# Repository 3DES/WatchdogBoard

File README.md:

Watchdog PCB, has 8 outputs and 4 inputs. The first output is used as watchdog output and will be switched off if not triggered regularely. Input 0 is the watchdog readback to check if the watchdog can still switch off the output 0 relay.

The relays are powered via USB 5V, what, depending on the used USB cable, can be a bit less sometimes. If you have problems with that change the USB cable or change the layout:

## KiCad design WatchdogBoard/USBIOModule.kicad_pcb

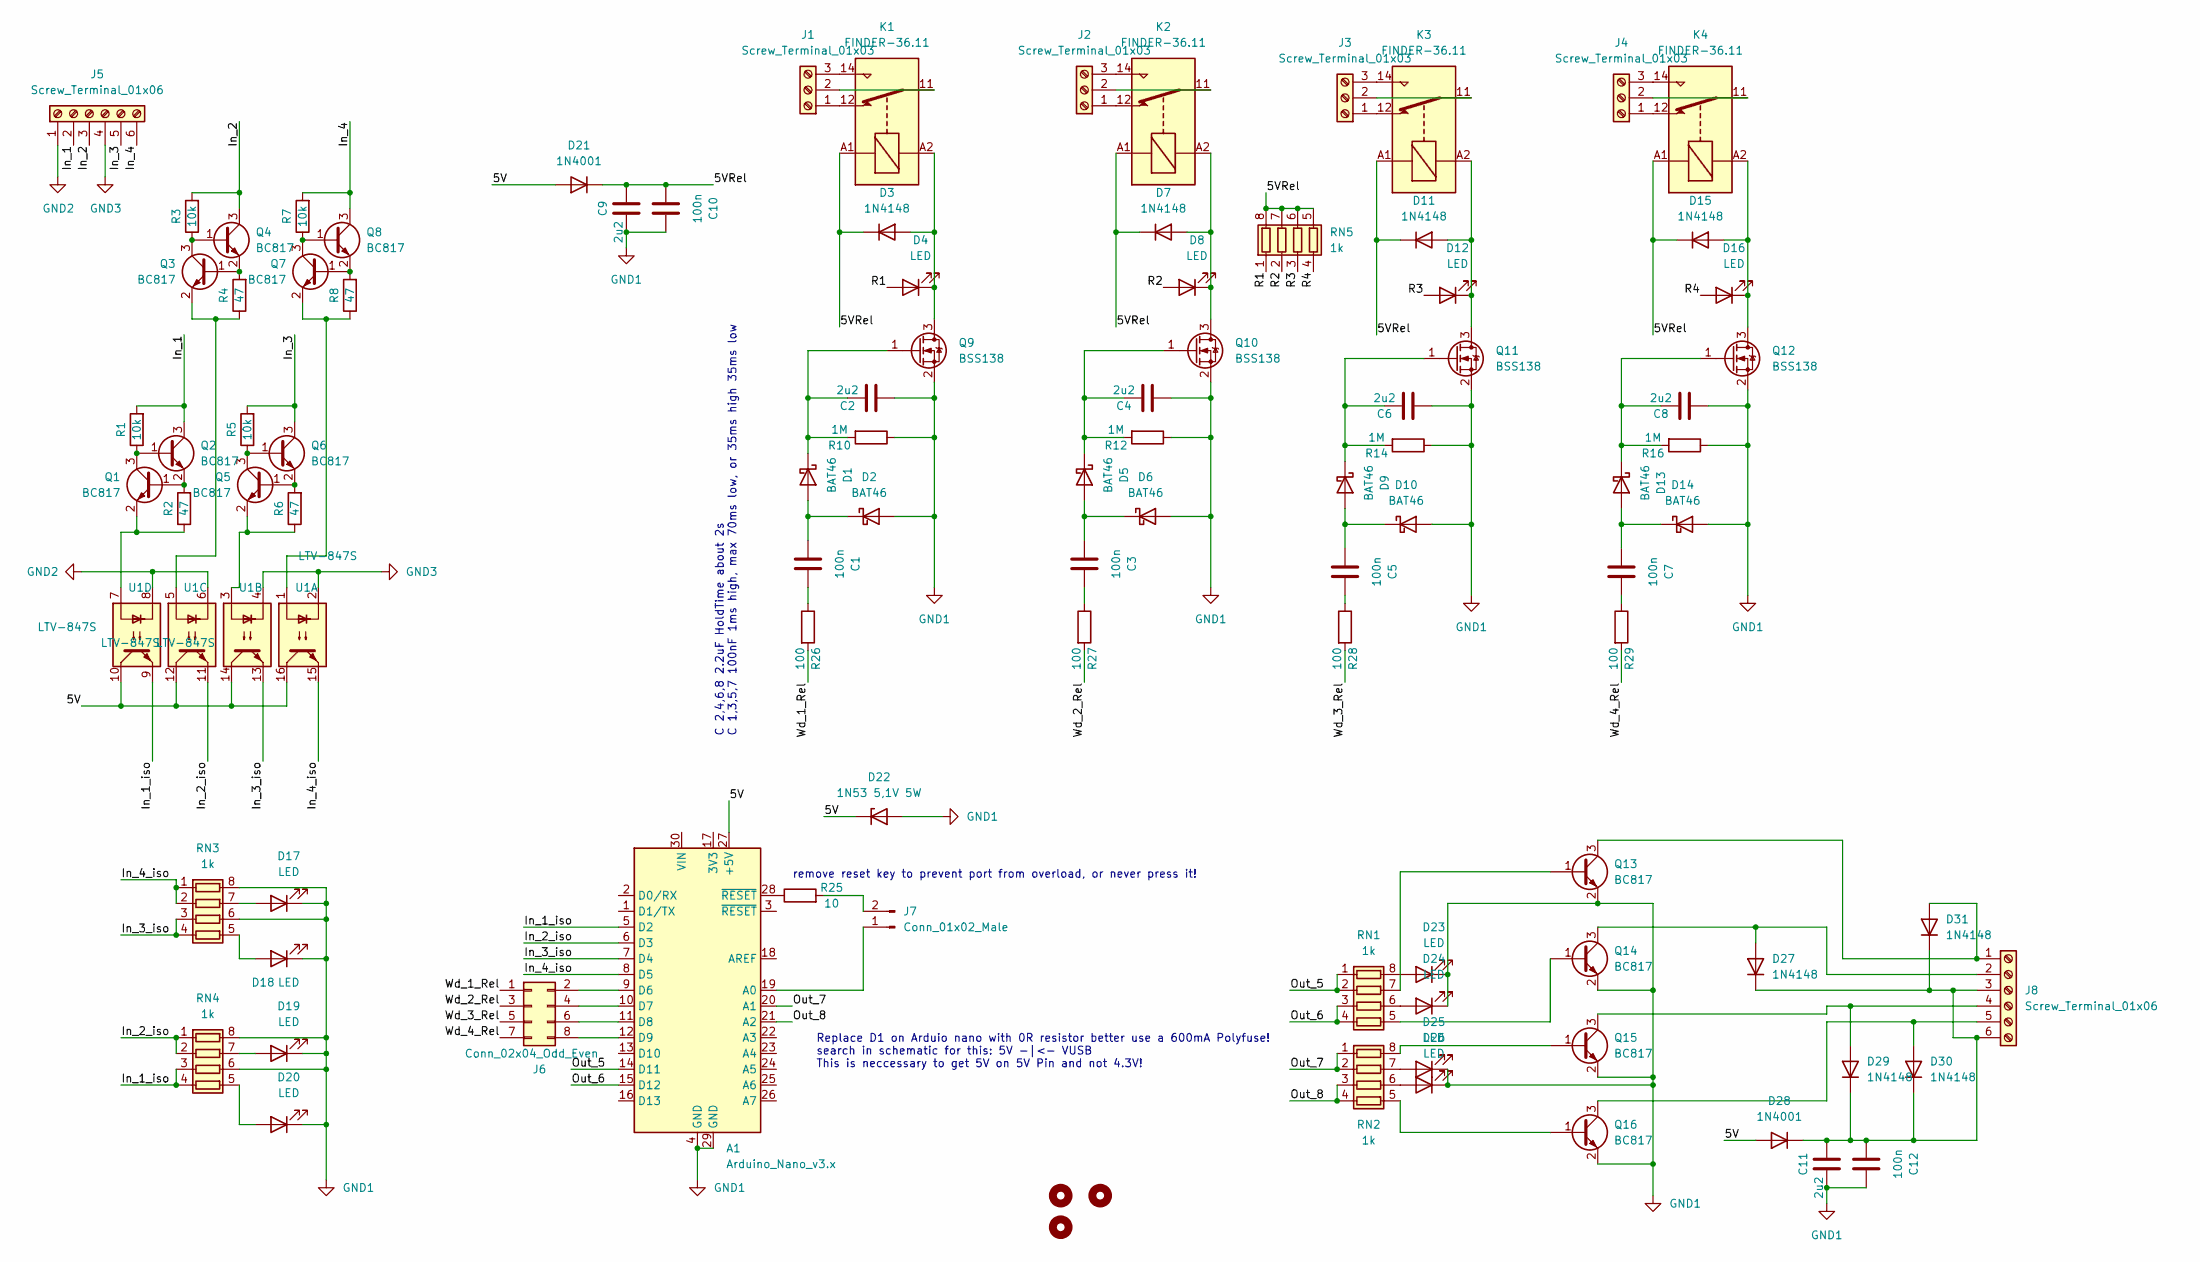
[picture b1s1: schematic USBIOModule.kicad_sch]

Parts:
A1: Arduino_Nano_v3.x; Arduino_Nano
C1, C3, C5, C7, C10, C12: 100n; C_0603_1608Metric
C2, C4, C6, C8, C9, C11: 2u2; C_0603_1608Metric
D1, D2, D5, D6, D9, D10, D13, D14: BAT46; D_SOD-123
D3, D7, D11, D15, D27, D29, D30, D31: 1N4148; D_MiniMELF
D4, D8, D12, D16, D17, D18, D19, D20, D23, D24, D25, D26: LED; LED_0603_1608Metric
D21, D28: 1N4001; D_DO-41_SOD81_P10.16mm_Horizontal
D22: 1N53 5,1V 5W; D_DO-41_SOD81_P10.16mm_Horizontal
H1, H2, H3: MountingHole; MountingHole_3.2mm_M3
J1, J2, J3, J4: Screw_Terminal_01x03; TerminalBlock_bornier-3_P5.08mm
J5, J8: Screw_Terminal_01x06; TerminalBlock_bornier-6_P5.08mm
J6: Conn_02x04_Odd_Even; PinHeader_2x04_P2.54mm_Vertical
J7: Conn_01x02_Male; PinHeader_1x02_P2.54mm_Vertical
K1, K2, K3, K4: FINDER-36.11; Relay_SPDT_Finder_36.11
Q1, Q2, Q3, Q4, Q5, Q6, Q7, Q8, Q13, Q14, Q15, Q16: BC817; SOT-23
Q9, Q10, Q11, Q12: BSS138; SOT-23
R1, R3, R5, R7: 10k; R_0603_1608Metric
R2, R4, R6, R8: 47; R_0603_1608Metric
R10, R12, R14, R16: 1M; R_0603_1608Metric
R25: 10; R_0603_1608Metric
R26, R27, R28, R29: 100; R_0603_1608Metric
RN1, RN2, RN3, RN4, RN5: 1k; R_Array_Convex_4x0612
U1: LTV-847S; SMDIP-16_W9.53mm

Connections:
/5V: A1.27 (+5V), D21.2 (A), D22.1 (K), D28.2 (A), U1.10, U1.12, U1.14, U1.16
/5VRel: C9.2, C10.1, D3.1 (K), D7.1 (K), D11.1 (K), D15.1 (K), D21.1 (K), K1.A1, K2.A1, K3.A1, K4.A1, RN5.5 (R4.2), RN5.6 (R3.2), RN5.7 (R2.2), RN5.8 (R1.2)
/In_1: J5.2, Q2.3 (C), R1.2
/In_1_iso: A1.5 (D2), RN4.3 (R3.1), RN4.4 (R4.1), U1.9
/In_2: J5.3, Q4.3 (C), R3.2
/In_2_iso: A1.6 (D3), RN4.1 (R1.1), RN4.2 (R2.1), U1.11
/In_3: J5.5, Q6.3 (C), R5.2
/In_3_iso: A1.7 (D4), RN3.3 (R3.1), RN3.4 (R4.1), U1.13
/In_4: J5.6, Q8.3 (C), R7.2
/In_4_iso: A1.8 (D5), RN3.1 (R1.1), RN3.2 (R2.1), U1.15
/Out_5: A1.14 (D11), RN1.1 (R1.1), RN1.2 (R2.1)
/Out_6: A1.15 (D12), RN1.3 (R3.1), RN1.4 (R4.1)
/Out_7: A1.20 (A1), RN2.1 (R1.1), RN2.2 (R2.1)
/Out_8: A1.21 (A2), RN2.3 (R3.1), RN2.4 (R4.1)
/R1: D4.2 (A), RN5.1 (R1.1)
/R2: D8.2 (A), RN5.2 (R2.1)
/R3: D12.2 (A), RN5.3 (R3.1)
/R4: D16.2 (A), RN5.4 (R4.1)
/Wd_1_Rel: J6.1, R26.2
/Wd_2_Rel: J6.3, R27.2
/Wd_3_Rel: J6.5, R28.2
/Wd_4_Rel: J6.7, R29.2
GND1: A1.4 (GND), A1.29 (GND), C2.2, C4.2, C6.2, C8.2, C9.1, C10.2, C11.1, C12.2, D2.2 (A), D6.2 (A), D10.2 (A), D14.2 (A), D17.1 (K), D18.1 (K), D19.1 (K), D20.1 (K), D22.2 (A), D23.1 (K), D24.1 (K), D25.1 (K), D26.1 (K), Q9.2 (S), Q10.2 (S), Q11.2 (S), Q12.2 (S), Q13.2 (E), Q14.2 (E), Q15.2 (E), Q16.2 (E), R10.1, R12.1, R14.1, R16.1, RN3.6 (R3.2), RN3.8 (R1.2), RN4.6 (R3.2), RN4.8 (R1.2)
GND2: J5.1, U1.6, U1.8
GND3: J5.4, U1.2, U1.4
unnamed: A1.9 (D6), J6.2
unnamed: A1.10 (D7), J6.4
unnamed: A1.11 (D8), J6.6
unnamed: A1.12 (D9), J6.8
unnamed: A1.19 (A0), J7.1
unnamed: A1.28 (~RESET), R25.1
unnamed: C1.1, D1.2 (A), D2.1 (K)
unnamed: C1.2, R26.1
unnamed: C2.1, D1.1 (K), Q9.1 (G), R10.2
unnamed: C3.1, D5.2 (A), D6.1 (K)
unnamed: C3.2, R27.1
unnamed: C4.1, D5.1 (K), Q10.1 (G), R12.2
unnamed: C5.1, D9.2 (A), D10.1 (K)
unnamed: C5.2, R28.1
unnamed: C6.1, D9.1 (K), Q11.1 (G), R14.2
unnamed: C7.1, D13.2 (A), D14.1 (K)
unnamed: C7.2, R29.1
unnamed: C8.1, D13.1 (K), Q12.1 (G), R16.2
unnamed: C11.2, C12.1, D27.1 (K), D28.1 (K), D29.1 (K), D30.1 (K), D31.1 (K), J8.3, J8.6
unnamed: D3.2 (A), D4.1 (K), K1.A2, Q9.3 (D)
unnamed: D7.2 (A), D8.1 (K), K2.A2, Q10.3 (D)
unnamed: D11.2 (A), D12.1 (K), K3.A2, Q11.3 (D)
unnamed: D15.2 (A), D16.1 (K), K4.A2, Q12.3 (D)
unnamed: D17.2 (A), RN3.7 (R2.2)
unnamed: D18.2 (A), RN3.5 (R4.2)
unnamed: D19.2 (A), RN4.7 (R2.2)
unnamed: D20.2 (A), RN4.5 (R4.2)
unnamed: D23.2 (A), RN1.8 (R1.2)
unnamed: D24.2 (A), RN1.6 (R3.2)
unnamed: D25.2 (A), RN2.7 (R2.2)
unnamed: D26.2 (A), RN2.6 (R3.2)
unnamed: D27.2 (A), J8.2, Q14.3 (C)
unnamed: D29.2 (A), J8.4, Q15.3 (C)
unnamed: D30.2 (A), J8.5, Q16.3 (C)
unnamed: D31.2 (A), J8.1, Q13.3 (C)
unnamed: J1.1, K1.12
unnamed: J1.2, K1.11
unnamed: J1.3, K1.14
unnamed: J2.1, K2.12
unnamed: J2.2, K2.11
unnamed: J2.3, K2.14
unnamed: J3.1, K3.12
unnamed: J3.2, K3.11
unnamed: J3.3, K3.14
unnamed: J4.1, K4.12
unnamed: J4.2, K4.11
unnamed: J4.3, K4.14
unnamed: J7.2, R25.2
unnamed: Q1.1 (B), Q2.2 (E), R2.2
unnamed: Q1.2 (E), R2.1, U1.7
unnamed: Q1.3 (C), Q2.1 (B), R1.1
unnamed: Q3.1 (B), Q4.2 (E), R4.2
unnamed: Q3.2 (E), R4.1, U1.5
unnamed: Q3.3 (C), Q4.1 (B), R3.1
unnamed: Q5.1 (B), Q6.2 (E), R6.2
unnamed: Q5.2 (E), R6.1, U1.3
unnamed: Q5.3 (C), Q6.1 (B), R5.1
unnamed: Q7.1 (B), Q8.2 (E), R8.2
unnamed: Q7.2 (E), R8.1, U1.1
unnamed: Q7.3 (C), Q8.1 (B), R7.1
unnamed: Q13.1 (B), RN1.7 (R2.2)
unnamed: Q14.1 (B), RN1.5 (R4.2)
unnamed: Q15.1 (B), RN2.8 (R1.2)
unnamed: Q16.1 (B), RN2.5 (R4.2)

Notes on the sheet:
C 2,4,6,8 2.2uF HoldTime about 2s C 1,3,5,7 100nF 1ms high, max 70ms low, or 35ms high 35ms low
Replace D1 on Arduio nano with 0R resistor better use a 600mA Polyfuse! search in schematic for this: 5V -|<- VUSB This is neccessary to get 5V on 5V Pin and not 4.3V!
remove reset key to prevent port from overload, or never press it!

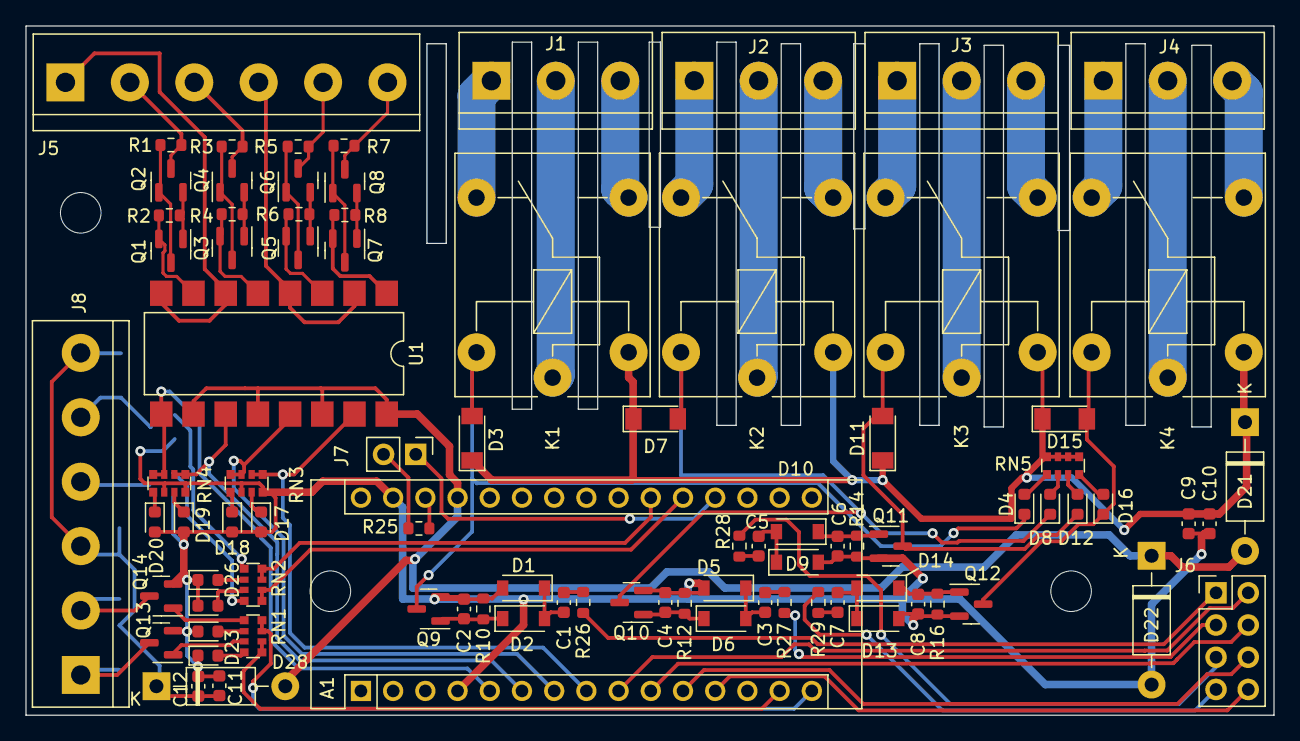
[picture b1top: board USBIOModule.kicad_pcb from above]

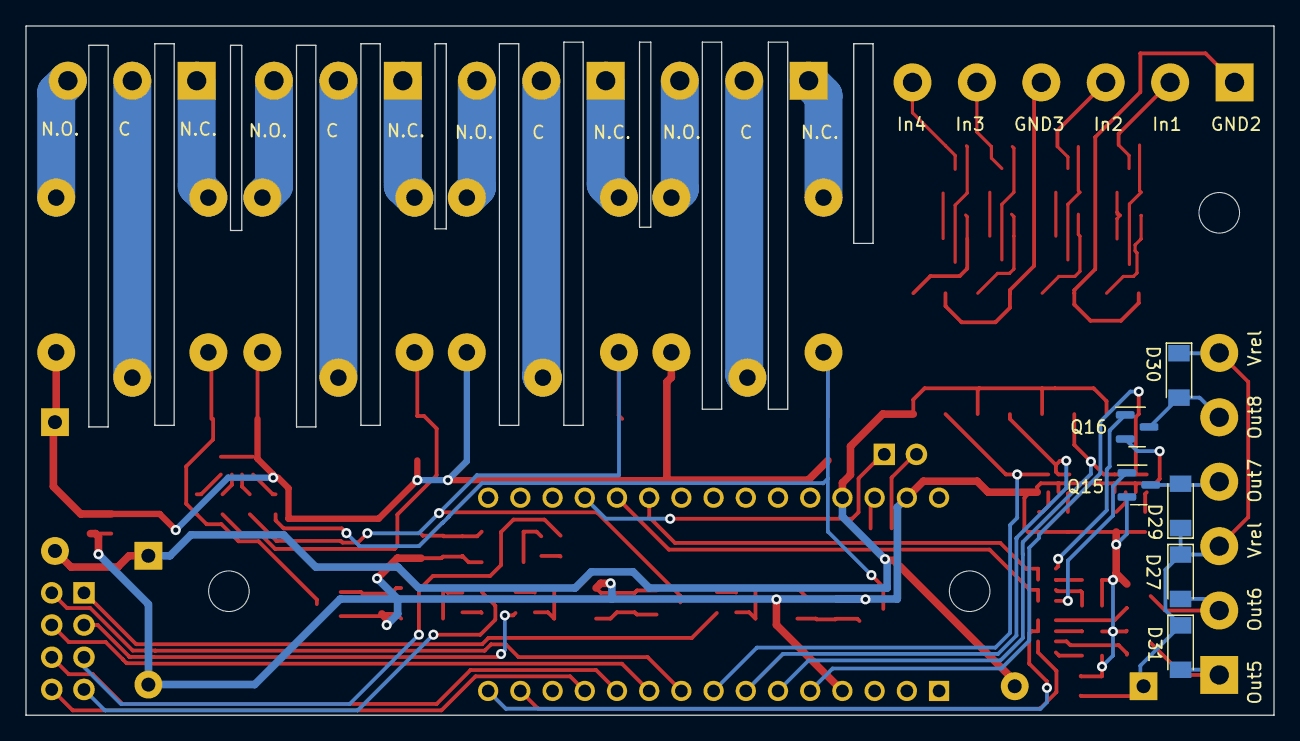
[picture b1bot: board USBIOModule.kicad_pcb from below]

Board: 2 copper layers, 98.4 x 54.4 mm, 98 parts (6 on the bottom side), 89 nets.

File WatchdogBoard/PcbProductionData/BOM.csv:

"ID";"Bezeichner";"Gehäuse";"Stückzahl";"Bezeichnung";"Anbieter und Referenz";
1;"J5,J8";"TerminalBlock_bornier-6_P5.08mm";2;"Screw_Terminal_01x06";;;
2;"RN1,RN5,RN2,RN4,RN3";"R_Array_Convex_4x0612";5;"1k";;;
3;"K4,K2,K1,K3";"Relay_SPDT_Finder_36.11";4;"FINDER-36.11";;;
4;"Q9,Q10,Q12,Q11";"SOT-23";4;"BSS138";;;
5;"D3,D11,D7,D15,D29,D30,D31,D27";"D_MiniMELF";8;"1N4148";;;
6;"R2,R6,R4,R8";"R_0603_1608Metric";4;"47";;;
7;"Q5,Q3,Q8,Q14,Q2,Q6,Q7,Q1,Q13,Q4,Q15,Q16";"SOT-23";12;"BC817";;;
8;"R1,R7,R3,R5";"R_0603_1608Metric";4;"10k";;;
9;"D19,D4,D26,D17,D16,D12,D8,D23,D18,D20,D25,D24";"LED_0603_1608Metric";12;"LED";;;
10;"U1";"SMDIP-16_W9.53mm";1;"LTV-847S";;;
11;"R25,R29,R28,R26,R27";"R_0603_1608Metric";5;"100";;;
12;"R14,R12,R16,R10";"R_0603_1608Metric";4;"1M";;;
13;"J2,J4,J3,J1";"TerminalBlock_bornier-3_P5.08mm";4;"Screw_Terminal_01x03";;;
14;"H3,H1,H2";"MountingHole_3.2mm_M3";3;"MountingHole";;;
15;"A1";"Arduino_Nano";1;"Arduino_Nano_v3.x";;;
16;"D22";"D_DO-41_SOD81_P10.16mm_Horizontal";1;"1N53 5,1V 5W";;;
17;"D14,D1,D2,D9,D13,D6,D5,D10";"D_SOD-123";8;"BAT46";;;
18;"D21,D28";"D_DO-41_SOD81_P10.16mm_Horizontal";2;"1N4001";;;
19;"C8,C4,C11,C2,C6,C9";"C_0603_1608Metric";6;"2u2";;;
20;"C10,C5,C1,C3,C7,C12";"C_0603_1608Metric";6;"100n";;;
21;"J6";"PinHeader_2x04_P2.54mm_Vertical";1;"Conn_02x04_Odd_Even";;;
22;"J7";"PinHeader_1x02_P2.54mm_Vertical";1;"Conn_01x02_Male";;;

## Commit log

2022-12-18 watchdog is working, relays are working, inputs are readable
2022-12-26 COM port set in platformio.ini
2022-12-26 debug improved, reset lock added, tick time calculation improved, refactored
2022-12-26 all outputs are switched OFF in error case, outputs switched synchronized, arduino LED shows watchdog state
2022-12-26 refactored, setup calls fixed, reset lock fixed
2023-04-02 single step CRC fixed, new command V added, request and response are no longer identical
2023-04-02 hex file added
2023-04-10 watchdog improved, D command added
2023-04-11 bug in watchdog_getWatchdog() fixed
2023-04-11 self test simplified and fixed by monitoring expected state for several milliseconds now
2023-04-20 identifiers refactored
2023-04-20 wrong error number fixed, little refactored, calculated CRC is sent back in NACK message now to simplify testing
2023-06-09 outputs switched OFF in case of watchdog error, lock release should work
2023-11-04 Watchdog trigger command returns lock state now for better diagnosis, lock release improved
2024-02-27 fast retrigger implemented, ALWAYS_RUNNING version added, DEBUG version added
2024-09-29 Add watchdog board schematic
2026-01-05 added PCB and schematic as jpg for easier accessability
2026-03-14 png added that shows how to solve 5V problem with USB power supply
